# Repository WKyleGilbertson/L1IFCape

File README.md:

L1IFCape

===

This project (hardware and software) is licensed under CERN-OHL-S and GPLv3 for open-source, academic, and personal use. Commercial licensing is available. If you wish to integrate this receiver into a closed-source, proprietary, or commercial product without the reciprocal open-source obligations, please email contact@navstargps.us to purchase a commercial license.

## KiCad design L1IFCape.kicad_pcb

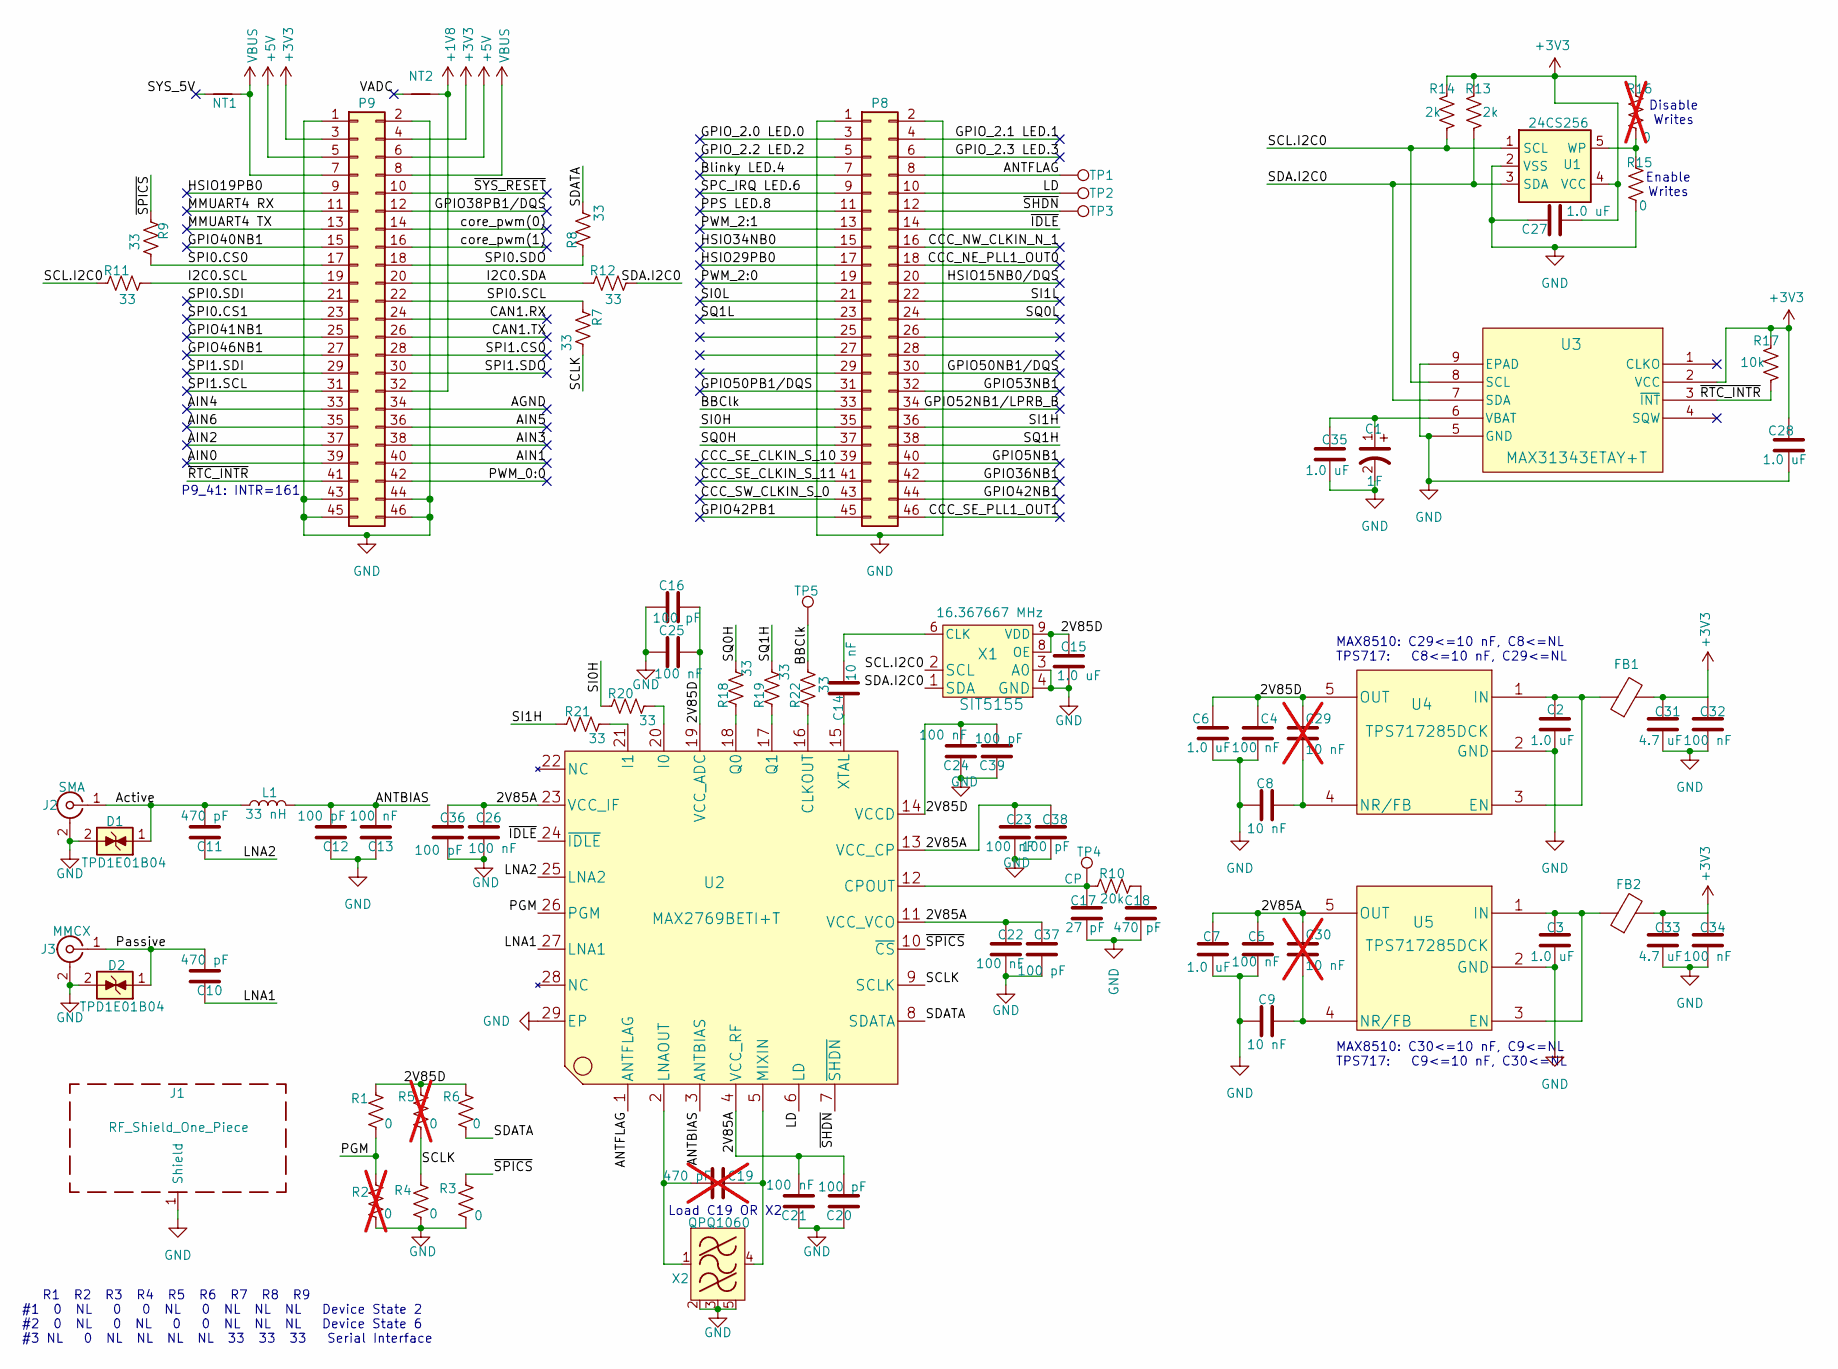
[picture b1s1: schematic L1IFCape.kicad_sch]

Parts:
C1: 1F; KR5R5C105R; MANUFACTURER_PART_NUMBER KW-5R5C334-R; MOUSER_PART_NUMBER 504-KW-5R5C334-R
C2, C3, C6, C7, C15, C27, C28, C35: 1.0 uF; C_0603_1608Metric; MPN GCM188R71C105KA64D
C4, C5, C13, C21, C22, C23, C24, C25, C26: 100 nF; C_0603_1608Metric; MPN C0603C104K5RACAUTO
C8, C9, C14: 10 nF; C_0603_1608Metric; MPN C0603C103F3GECAUTO
C10, C11, C18: 470 pF; C_0603_1608Metric; MPN GCM1885C2A471FA16D
C12, C16, C20, C36, C37, C38, C39: 100 pF; C_0603_1608Metric; MPN GCM1885C2A101FA16D
C17: 27 pF; C_0603_1608Metric; MPN C0603C270F3HACAUTO
C19: 470 pF; C_0603_1608Metric; MPN GCM1885C2A471FA16D; not fitted
C29, C30: 10 nF; C_0603_1608Metric; MPN C0603C103F3GECAUTO; not fitted
C31, C33: 4.7 uF; C_0805_2012Metric; MPN C0805C475J8RACAUTO
C32, C34: 100 nF; C_0805_2012Metric; MPN C0805C104K8RACTU
D1, D2: TPD1E01B04; Texas_DPY0002A_0.6x1mm_P0.65mm; MPN TPD1E01B04DPYRQ1
FB1, FB2: Ferrite_Bead; C_0805_2012Metric; MPN BLM21AG102SZ1D
J1: RF_Shield_One_Piece; Laird_Technologies_BMI-S-103_26.21x26.21mm; MPN BMI-S-103
J2: SMA; SMA_Amphenol_901-143_Horizontal; MPN 901-143
J3: MMCX; MMCX_Molex_73415-1471_Vertical; MPN 908-22106
L1: 33 nH; L_0603_1608Metric; MPN LQG18HH33NJ00D
NT1, NT2: NetTie_2
P8, P9: BeagleBone_Black_Header; PinHeader_2x23_P2.54mm_Vertical; MPN SSQ-123-23-G-D
R1, R3, R4, R6, R15: 0; R_0603_1608Metric; MPN ERJ-3GEY0R00V
R2, R5, R16: 0; R_0603_1608Metric; MPN ERJ-3GEY0R00V; not fitted
R7, R8, R9, R11, R12, R18, R19, R20, R21, R22: 33; R_0603_1608Metric; MPN ERJ-3EKF33R0V
R10: 20k; R_0603_1608Metric; MPN ERJ-3EKF2002V
R13, R14: 2k; R_0603_1608Metric; MPN ERJ-3EKF2001V
R17: 10k; R_0603_1608Metric; MPN ERJ-3EKF1002V
TP1: ANTFLAG; TestPoint_THTPad_D1.5mm_Drill0.7mm
TP2: LD; TestPoint_THTPad_D1.5mm_Drill0.7mm
TP3: ~{SHDN}; TestPoint_THTPad_D1.5mm_Drill0.7mm
TP4: CP; TestPoint_Pad_D1.0mm
TP5: BBClk; TestPoint_THTPad_D1.5mm_Drill0.7mm
U1: 24CS256; SOT-23-5; MPN 24CS256T-I/OT
U2: MAX2769BETI+T; QFN-28_EP_5.63x5.63_Pitch0.5mm; MPN MAX2769BETI/V+T
U3: MAX31343ETAY+T; MAX31343_TDFN; MPN MAX31343ETAY+T
U4, U5: TPS717285DCK; MPN TPS717285DCK
X1: SIT5155; 10L_CQFN; MPN SiT5155AICFKG28IT-16.367667
X2: QPQ1060; QPQ1060_1.4x1.2; MPN QPQ1060SR

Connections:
+1V8: NT2.2, P9.32
+3V3: C27.1, C28.1, C31.1, C32.1, C33.1, C34.1, FB1.2, FB2.2, P9.3, P9.4, R13.1, R14.1, R16.2, R17.1, U1.4 (VCC), U3.2 (VCC)
+5V: P9.5, P9.6
/2V85A: C5.1, C7.1, C20.2, C21.2, C22.1, C23.2, C26.1, C30.1, C36.1, C37.1, C38.2, U2.4 (VCC_RF), U2.11 (VCC_VCO), U2.13 (VCC_CP), U2.23 (VCC_IF), U5.5 (OUT)
/AGND: P9.34
/AIN0: P9.39
/AIN1: P9.40
/AIN2: P9.37
/AIN3: P9.38
/AIN4: P9.33
/AIN5: P9.36
/AIN6: P9.35
/ANTBIAS: C12.2, C13.2, L1.1, U2.3 (ANTBIAS)
/ANTFLAG: P8.8, TP1.1 (1_1), U2.1 (ANTFLAG)
/Active: C11.2, D1.1 (K), J2.1 (In), L1.2
/BBClk: P8.33, R22.2, TP5.1 (1_1)
/Blinky LED.4: P8.7
/CAN1.RX: P9.24
/CAN1.TX: P9.26
/CCC_NE_PLL1_OUT0: P8.18
/CCC_NW_CLKIN_N_1: P8.16
/CCC_SE_CLKIN_S_10: P8.39
/CCC_SE_CLKIN_S_11: P8.41
/CCC_SE_PLL1_OUT1: P8.46
/CCC_SW_CLKIN_S_0: P8.43
/GPIO5NB1: P8.40
/GPIO36NB1: P8.42
/GPIO38PB1/DQS: P9.12
/GPIO40NB1: P9.15
/GPIO41NB1: P9.25
/GPIO42NB1: P8.44
/GPIO42PB1: P8.45
/GPIO46NB1: P9.27
/GPIO50NB1/DQS: P8.30
/GPIO50PB1/DQS: P8.31
/GPIO52NB1/LPRB_B: P8.34
/GPIO53NB1: P8.32
/GPIO_2.0 LED.0: P8.3
/GPIO_2.1 LED.1: P8.4
/GPIO_2.2 LED.2: P8.5
/GPIO_2.3 LED.3: P8.6
/HSIO15NB0/DQS: P8.20
/HSIO19PB0: P9.9
/HSIO29PB0: P8.17
/HSIO34NB0: P8.15
/I2C0.SCL: P9.19, R11.2
/I2C0.SDA: P9.20, R12.1
/LD: P8.10, TP2.1 (1_1), U2.6 (LD)
/LNA1: C10.1, U2.27 (LNA1)
/LNA2: C11.1, U2.25 (LNA2)
/MMUART4 RX: P9.11
/MMUART4 TX: P9.13
/PGM: R1.2, R2.1, U2.26 (PGM)
/PPS LED.8: P8.11
/PWM_0:0: P9.42
/PWM_2:0: P8.19
/PWM_2:1: P8.13
/Passive: C10.2, D2.1 (K), J3.1 (In)
/SCL.I2C0: R11.1, R14.2, U1.1 (SCL), U3.8 (SCL), X1.2 (SCL)
/SCLK: R4.2, R5.2, R7.2, U2.9 (SCLK)
/SDATA: R6.2, R8.2, U2.8 (SDATA)
/SI0H: P8.35, R20.1
/SI0L: P8.21
/SI1H: P8.36, R21.2
/SI1L: P8.22
/SPC_IRQ LED.6: P8.9
/SPI0.CS0: P9.17, R9.2
/SPI0.CS1: P9.23
/SPI0.SCL: P9.22, R7.1
/SPI0.SDI: P9.21
/SPI0.SDO: P9.18, R8.1
/SPI1.CS0: P9.28
/SPI1.SCL: P9.31
/SPI1.SDI: P9.29
/SPI1.SDO: P9.30
/SQ0H: P8.37, R18.2
/SQ0L: P8.24
/SQ1H: P8.38, R19.2
/SQ1L: P8.23
/core_pwm(0): P9.14
/core_pwm(1): P9.16
/~IDLE: P8.14, U2.24 (~IDLE)
/~RTC_INTR: P9.41, R17.2, U3.3 (~INT)
/~SHDN: P8.12, TP3.1 (1_1), U2.7 (~SHDN)
/~SPICS: R3.2, R9.1, U2.10 (~CS)
/~SYS_RESET: P9.10
GND: C1.2, C2.2, C3.2, C4.2, C5.2, C6.2, C7.2, C8.1, C9.1, C12.1, C13.1, C15.2, C16.1, C17.2, C18.2, C20.1, C21.1, C22.2, C23.1, C24.1, C25.1, C26.2, C27.2, C28.2, C31.2, C32.2, C33.2, C34.2, C35.2, C36.2, C37.2, C38.1, C39.1, D1.2 (A), D2.2 (A), J1.1 (Shield_1), J2.2 (Ext), J3.2 (Ext), P8.1, P8.2, P9.1, P9.2, P9.43, P9.44, P9.45, P9.46, R2.2, R3.1, R4.1, R15.1, U1.2 (VSS), U2.29 (EP), U3.5 (GND), U3.9 (EPAD), U4.2 (GND), U5.2 (GND), X1.3 (A0), X1.4 (GND), X1.5 (A0), X2.2 (GND), X2.3 (GND), X2.5 (GND); also elsewhere on the board
unnamed: C18.1, R10.2
unnamed: R15.2, R16.1, U1.5 (WP)
unnamed: R22.1, U2.16 (CLKOUT)
unnamed: C17.1, R10.1, TP4.1 (1_1), U2.12 (CPOUT)
unnamed: R20.2, U2.20 (I0)
unnamed: R21.1, U2.21 (I1)
unnamed: C19.2, U2.2 (LNAOUT), X2.1 (IN)
unnamed: C19.1, U2.5 (MIXIN), X2.4 (OUT)
unnamed: R18.1, U2.18 (Q0)
unnamed: R19.1, U2.17 (Q1)
unnamed: C14.2, U2.15 (XTAL)
unnamed: C1.1, C35.1, U3.6 (VBAT)
unnamed: C2.1, FB1.1, U4.1 (IN), U4.3 (EN)
unnamed: C8.2, C29.2, U4.4 (NR/FB)
unnamed: C3.1, FB2.1, U5.1 (IN), U5.3 (EN)
unnamed: C9.2, C30.2, U5.4 (NR/FB)
unnamed: C14.1, X1.6 (CLK)
VBUS: NT1.2, P9.7, P9.8

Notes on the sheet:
R1 R2 R3 R4 R5 R6 R7 R8 R9 #1 0 NL 0 0 NL 0 NL NL NL Device State 2 #2 0 NL 0 NL 0 0 NL NL NL Device State 6 #3 NL 0 NL NL NL NL 33 33 33 Serial Interface
Disable Writes
Load C19 OR X2
MAX8510: C29<=10 nF, C8<=NL TPS717: C8<=10 nF, C29<=NL
MAX8510: C30<=10 nF, C9<=NL TPS717: C9<=10 nF, C30<=NL
P9_41: INTR=161
Enable Writes

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
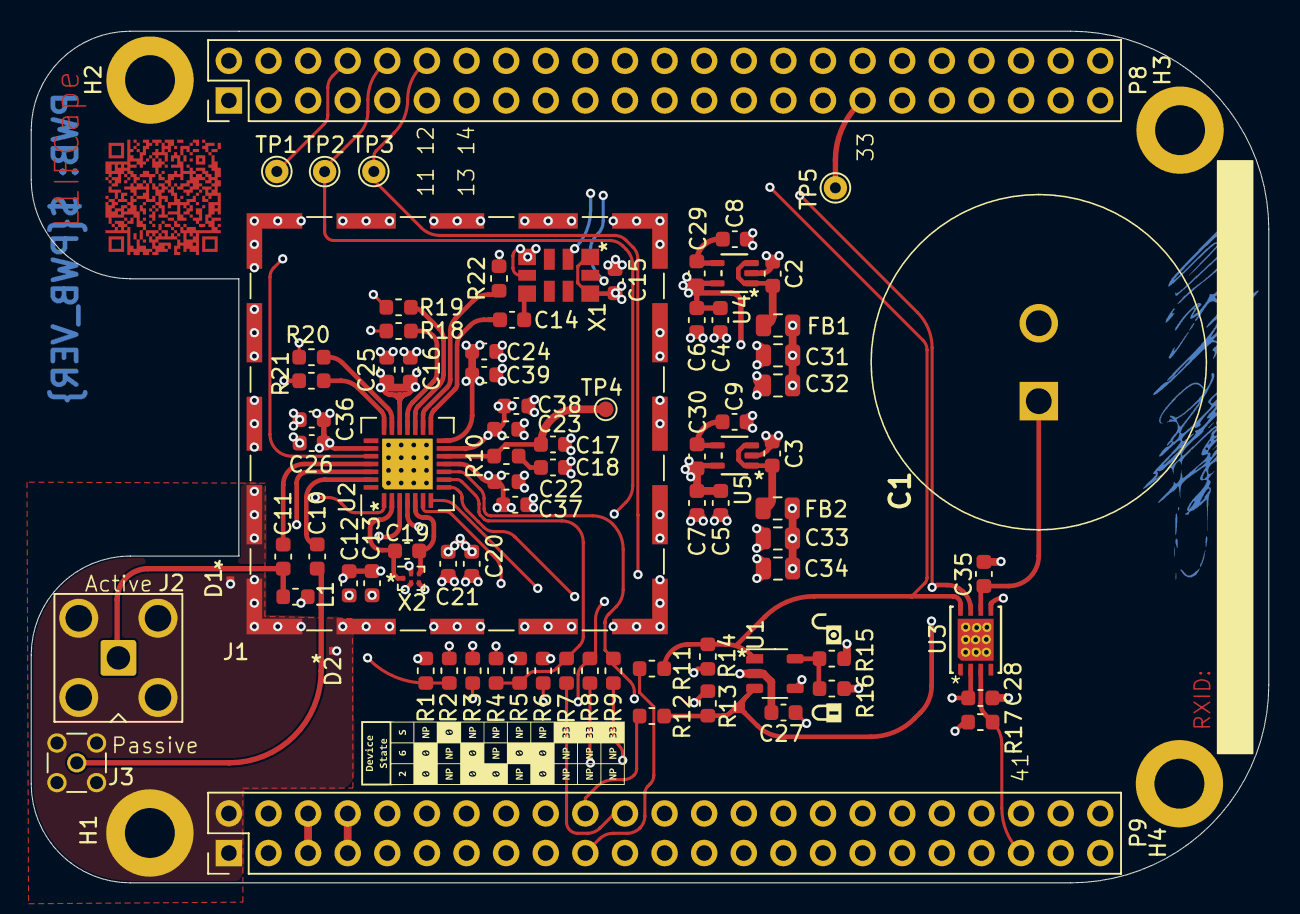
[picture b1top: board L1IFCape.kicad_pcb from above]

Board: 4 copper layers, 79.4 x 54.6 mm, 88 parts (0 on the bottom side), 49 nets.

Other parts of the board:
H1, H2, H3, H4: MountingHole_3.2mm_M3_DIN965_Pad
QR*****: QR-L1IFCape-8mm

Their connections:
GND: H1.1, H2.1, H3.1, H4.1; also elsewhere on the board

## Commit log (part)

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2025-12-09 Added Design Files
2025-12-09 Ignore some stuff
2025-12-10 Added CERN License
2025-12-10 Moved some parts around
2025-12-12 Added Padlock graphic and 1F Supercap
2026-03-05 Shorter Header Pins
2026-04-03 Ordered Rev2 from OSH Park
2026-05-22 Moved Antenna Ports, and changed resistor bias circuit

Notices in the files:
L1IFCape.kicad_pcb:
SPDX-License-Identifier: CERN-OHL-S-2.0
Licensed under the CERN Open Hardware Licence Version 2 - Strongly Reciprocal
https://cern.ch/cern-ohl
